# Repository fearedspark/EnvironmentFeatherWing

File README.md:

# Environmental Sensor Board Project

**`PCB Software`**: `KiCad`

This project is a Feather Wing board hosting a tempertature/humidity sensor and a volatile organic compounds/equivalent CO2 sensor from sensirion.  
This is also my first KiCad project.

## Important Parts

- T/RH Sensor: SHT31-DIS-F ([Datasheet](https://www.sensirion.com/fileadmin/user_upload/customers/sensirion/Dokumente/0_Datasheets/Humidity/Sensirion_Humidity_Sensors_SHT3x_Datasheet_digital.pdf))
- VOC/eCO2 Sensor: SGP30 ([Datasheet](https://www.sensirion.com/fileadmin/user_upload/customers/sensirion/Dokumente/0_Datasheets/Gas/Sensirion_Gas_Sensors_SGP30_Datasheet.pdf))
- 1.8V LDO Regulator: MCP1754S-1802E/CB ([Datasheet](http://ww1.microchip.com/downloads/en/DeviceDoc/20002276C.pdf))

## Power Supply

The sensors are powered from the 3.3V rail available on the feather wing headers.
The SGP30 sensor has an LDO to provide it with 1.8V.

## BOM

|Designator(s)         |Quantity|Manufacturer        |Part Number       |Description                    |Value|Tolerance|Rating|Package          |Type|Note|
|----------------------|:------:|--------------------|------------------|-------------------------------|-----|---------|------|-----------------|----|----|
|U1                    |1       |Sensirion AG        |SHT31-DIS-F       |Temperature/Humidity I2C Sensor|     |         |      |8-DFN (2.5x2.5)  |SMT |    |
|U2                    |1       |Microchip Technology|MCP1754ST-1802E/CB|1.8V LDO Voltage Regulator     |     |         |      |SOT-23A-3        |SMT |    |
|U3                    |1       |Sensirion AG        |SGP30             |TVOS/CO2eq I2C Sensor          |     |         |      |6-DFN (2.45x2.45)|SMT |    |
|Q1, Q2                |2       |ON Semiconductor    |BSS138            |N-Channel MOSFET, 50V, 220mA   |     |         |      |SOT-23           |SMT |    |
|C1, C3, C4            |3       |                    |                  |10µF, 6.3V, 0805               |10µF |≤±20%    |≥6.3V |0805             |SMT |    |
|C2, C5, C6            |3       |                    |                  |100nF, 6.3V, 0603              |100nF|≤±20%    |≥6.3V |0603             |SMT |    |
|R1, R2, R3, R4, R5, R6|6       |                    |                  |10kΩ, ±5%, 0603                |10kΩ |≤±5%     |      |0603             |SMT |    |

## TODO

- Might add an absolute pressure sensor in a next revision

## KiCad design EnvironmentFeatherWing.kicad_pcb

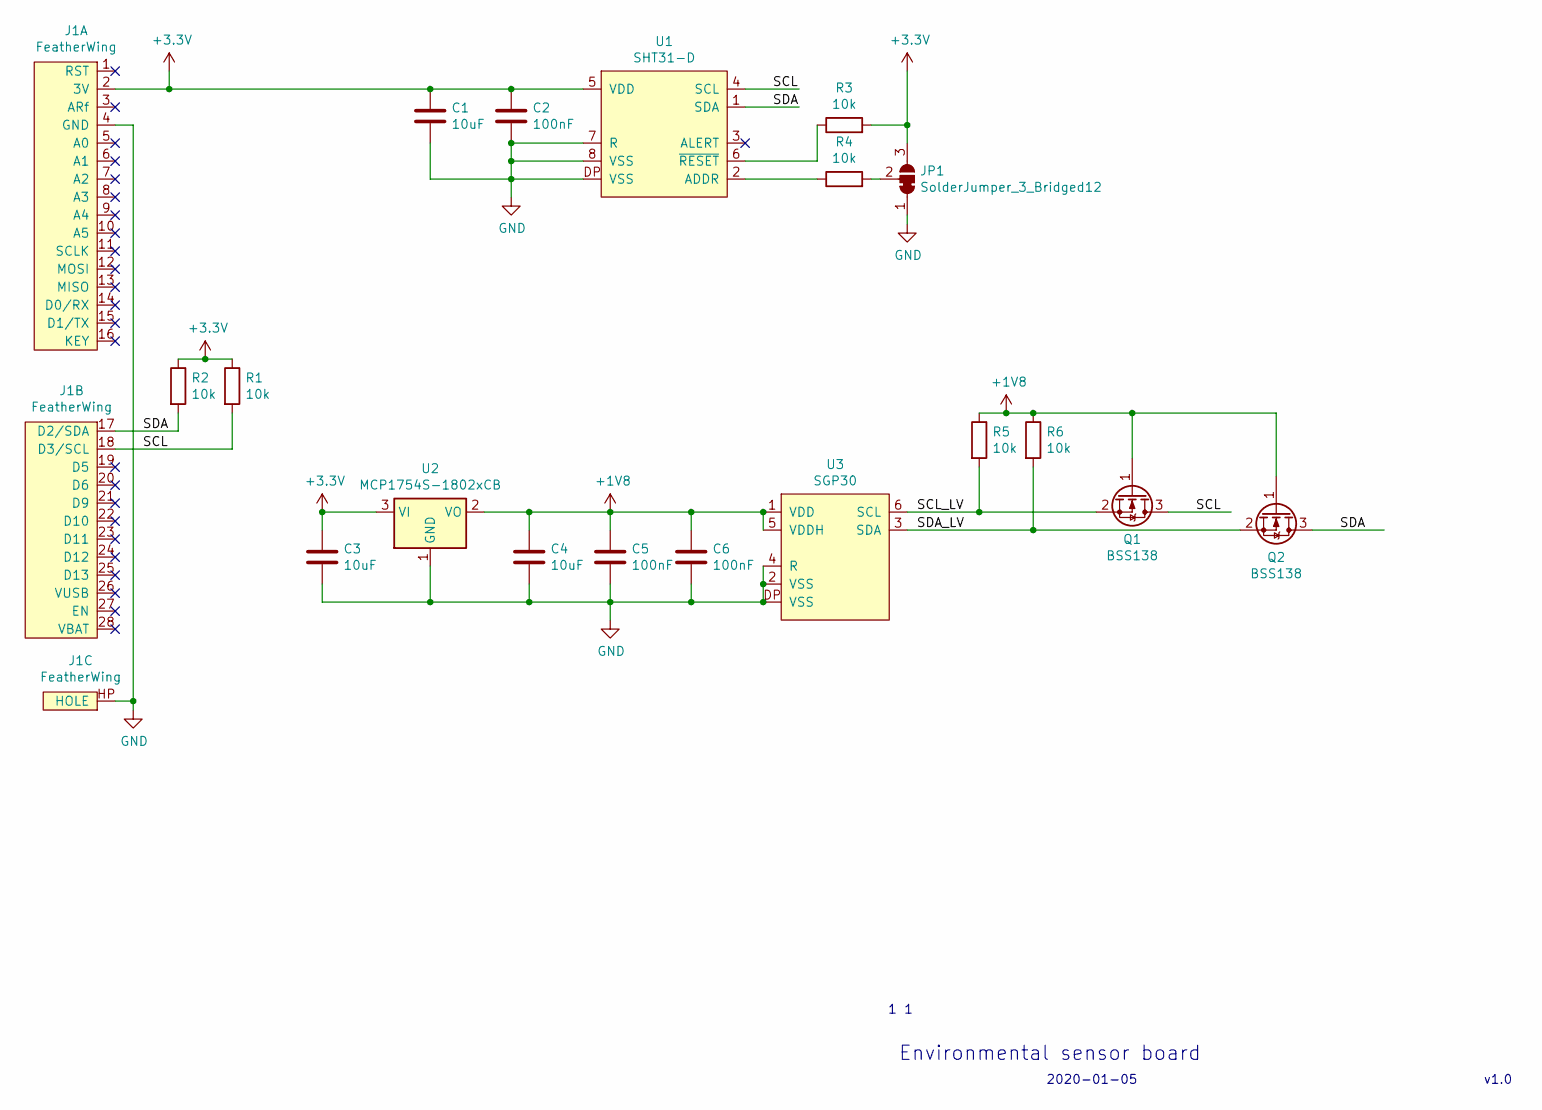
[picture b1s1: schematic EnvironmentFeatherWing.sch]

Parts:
C1, C3, C4: 10uF; C_0805_2012Metric
C2, C5, C6: 100nF; C_0603_1608Metric
J1: FeatherWing
JP1: SolderJumper_3_Bridged12; SolderJumper-3_P1.3mm_Bridged12_Pad1.0x1.5mm
Q1, Q2: BSS138; SOT-23
R1, R2, R3, R4, R5, R6: 10k; R_0603_1608Metric
U1: SHT31-D; DFN-8-2.5x2.5x0.9
U2: MCP1754S-1802xCB; SOT-23
U3: SGP30; DFN-6-2.45x2.45x0.9

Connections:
+1V8: C4.1, C5.1, C6.1, Q1.1 (G), Q2.1 (G), R5.1, R6.1, U2.2 (VO), U3.1 (VDD), U3.5 (VDDH)
+3V3: C1.1, C2.1, C3.1, J1.2 (3V), JP1.3 (B), R1.1, R2.1, R3.2, U1.5 (VDD), U2.3 (VI)
/SCL: J1.18 (D3/SCL), Q1.3 (D), R1.2, U1.4 (SCL)
/SCL_LV: Q1.2 (S), R5.2, U3.6 (SCL)
/SDA: J1.17 (D2/SDA), Q2.3 (D), R2.2, U1.1 (SDA)
/SDA_LV: Q2.2 (S), R6.2, U3.3 (SDA)
GND: C1.2, C2.2, C3.2, C4.2, C5.2, C6.2, J1.4 (GND), J1.HP (HOLE), JP1.1 (A), U1.7 (R), U1.8 (VSS), U1.DP (VSS), U2.1 (GND), U3.2 (VSS), U3.4 (R), U3.DP (VSS)
unnamed: JP1.2 (C), R4.2
unnamed: R3.1, U1.6 (~RESET)
unnamed: R4.1, U1.2 (ADDR)

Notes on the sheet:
Environmental sensor board
v1.0
2020-01-05

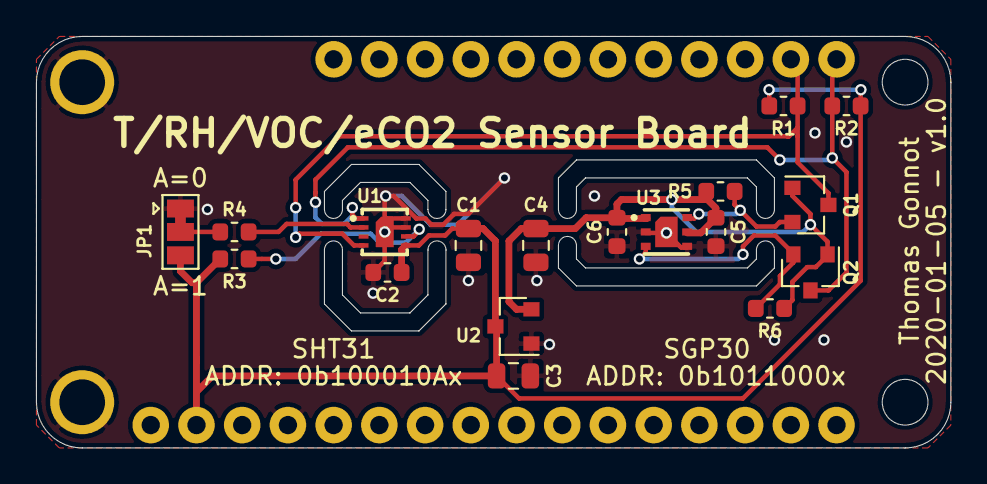
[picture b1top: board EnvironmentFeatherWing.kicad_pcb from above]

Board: 2 copper layers, 50.8 x 22.9 mm, 19 parts (0 on the bottom side), 10 nets.

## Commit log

2020-01-05 First revision
2020-01-05 Updated README with BOM
2020-01-05 Added missing library cache file
